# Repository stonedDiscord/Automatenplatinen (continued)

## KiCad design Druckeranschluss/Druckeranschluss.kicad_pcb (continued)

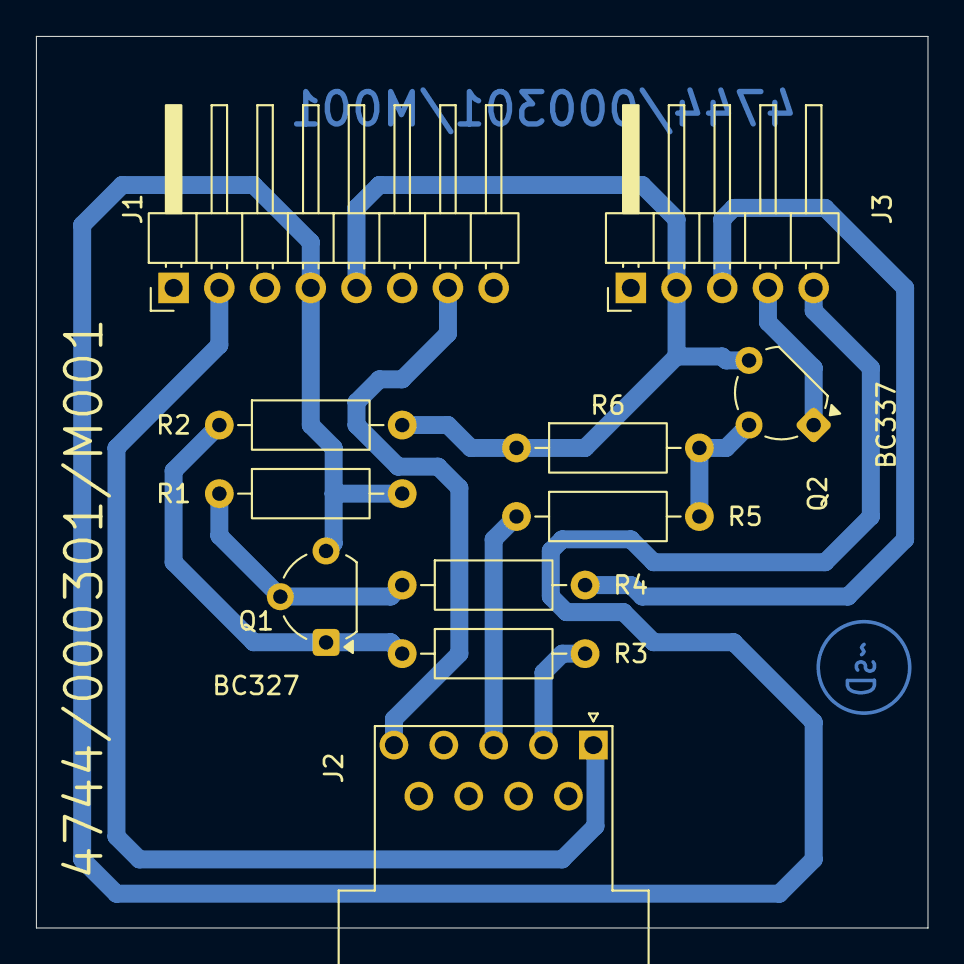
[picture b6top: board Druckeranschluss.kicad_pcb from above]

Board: 2 copper layers, 49.5 x 49.5 mm, 11 parts (0 on the bottom side), 11 nets.

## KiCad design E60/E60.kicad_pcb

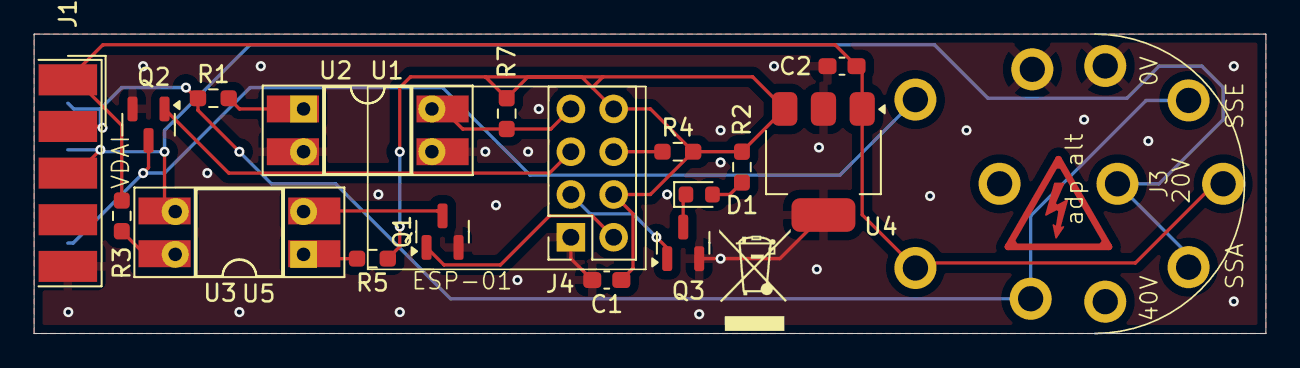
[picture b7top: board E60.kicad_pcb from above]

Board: 2 copper layers, 73.2 x 17.8 mm, 21 parts (1 on the bottom side), 18 nets.

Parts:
C1, C2: 1uF; C_0603_1608Metric_Pad1.08x0.95mm_HandSolder
D1: LED; LED_0603_1608Metric
J1: VDAI; DSUB-9_Male_EdgeMount_P2.77mm
J2: Bally/Bergmann; DIN45322
J3: ADP alt; DIN41524
J4: ESP-01; PinSocket_2x04_P2.54mm_Vertical
Q1, Q2, Q3: Q_NPN_BEC; SOT-23
R1: 4,7k; R_0603_1608Metric_Pad0.98x0.95mm_HandSolder
R2: 68; R_0603_1608Metric_Pad0.98x0.95mm_HandSolder
R3, R5, R7: 330; R_0603_1608Metric_Pad0.98x0.95mm_HandSolder
R4: 10k; R_0603_1608Metric_Pad0.98x0.95mm_HandSolder
U1, U3: PC817; DIP-4_W8.89mm_SMDSocket_LongPads
U2, U5: PC817; DIP-4_W7.62mm
U4: SPX2920M3-3.3_SOT223; SOT-223-3_TabPin2

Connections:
+3.3V: C1.1, J4.4, J4.8, R2.2, R4.2, R5.1, R7.1, U4.3 (VO)
+48V: J1.4, J3.1
BUSY: J1.9, J2.1, Q2.3 (C)
ESP_BUSY: J4.5, Q2.1 (B)
GND: C1.2, C2.2, J1.5, J2.2, J3.3, J4.1, Q1.2 (E), Q2.2 (E), Q3.2 (E), U1.2, U1.3, U2.2, U2.3, U4.2 (GND)
unnamed: D1.2 (A), R2.1
unnamed: D1.1 (K), Q3.3 (C)
unnamed: J4.3, Q3.1 (B)
unnamed: J4.6, R4.1
unnamed: Q1.3 (C), U3.2, U5.2
unnamed: R1.2, U1.1, U2.1
unnamed: R3.2, U3.4, U5.4
unnamed: R5.2, U3.1, U5.1
RX: J4.7, R7.2, U1.4, U2.4
RX1: J1.2, J1.6, J2.4, J3.5, R1.1
TX: J4.2, Q1.1 (B)
TX1: J1.3, J1.7, J2.3, J3.4, U3.3, U5.3
VPP: C2.1, J1.1, J2.5, J3.2, R3.1, U4.1 (VI)

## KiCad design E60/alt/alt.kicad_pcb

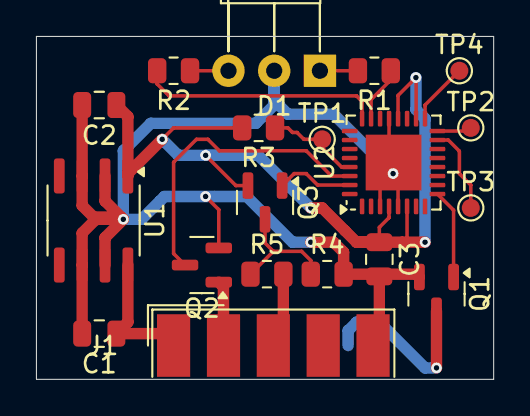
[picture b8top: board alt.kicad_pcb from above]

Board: 2 copper layers, 25.4 x 19.0 mm, 19 parts (0 on the bottom side), 18 nets.

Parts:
C1, C2, C3: C; C_0805_2012Metric
D1: LED_Dual_AKA; LED_D5.0mm-3_Horizontal_O3.81mm_Z3.0mm
J1: DE9_Plug; DSUB-9_Male_EdgeMount_P2.77mm
Q1, Q2: BCR533; SOT-23
Q3: BCR562; SOT-23
R1, R2: 271; R_0805_2012Metric
R3, R4: 472; R_0805_2012Metric
R5: 18A; R_0805_2012Metric
TP1, TP2, TP3, TP4: TestPoint; TestPoint_Pad_D1.0mm
U1: L78L05_SO8; SOIC-8_3.9x4.9mm_P1.27mm
U2: ATmega8A-M; QFN-32-1EP_5x5mm_P0.5mm_EP3.1x3.1mm

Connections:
GND: C1.2, C2.2, C3.2, D1.2 (K), J1.5, Q1.2 (E), Q2.2 (E), R4.2, U1.2 (GND), U1.3 (GND), U1.6 (GND), U1.7 (GND), U2.3 (GND), U2.5 (GND), U2.21 (AGND), U2.33 (GND)
unnamed: D1.1 (A1), R1.2
unnamed: D1.3 (A2), R2.1
unnamed: J1.3, R5.2
unnamed: Q1.1 (B), U2.9 (PD5)
unnamed: J1.9, Q1.3 (C)
unnamed: J1.2, Q2.1 (B)
unnamed: Q2.3 (C), U2.30 (PD0)
unnamed: Q3.1 (B), U2.31 (PD1)
unnamed: Q3.3 (C), R4.1, R5.1
unnamed: C1.1, J1.1, U1.8 (IN)
unnamed: TP3.1, U2.15 (PB3)
unnamed: TP2.1, U2.16 (PB4)
unnamed: TP4.1, U2.17 (PB5)
unnamed: R1.1, U2.23 (PC0)
unnamed: R2.2, U2.24 (PC1)
unnamed: R3.1, TP1.1, U2.29 (PC6/~RESET)
VCC: C2.1, C3.1, Q3.2 (E), R3.2, U1.1 (OUT), U2.4 (VCC), U2.6 (VCC), U2.18 (AVCC), U2.20 (AREF)
